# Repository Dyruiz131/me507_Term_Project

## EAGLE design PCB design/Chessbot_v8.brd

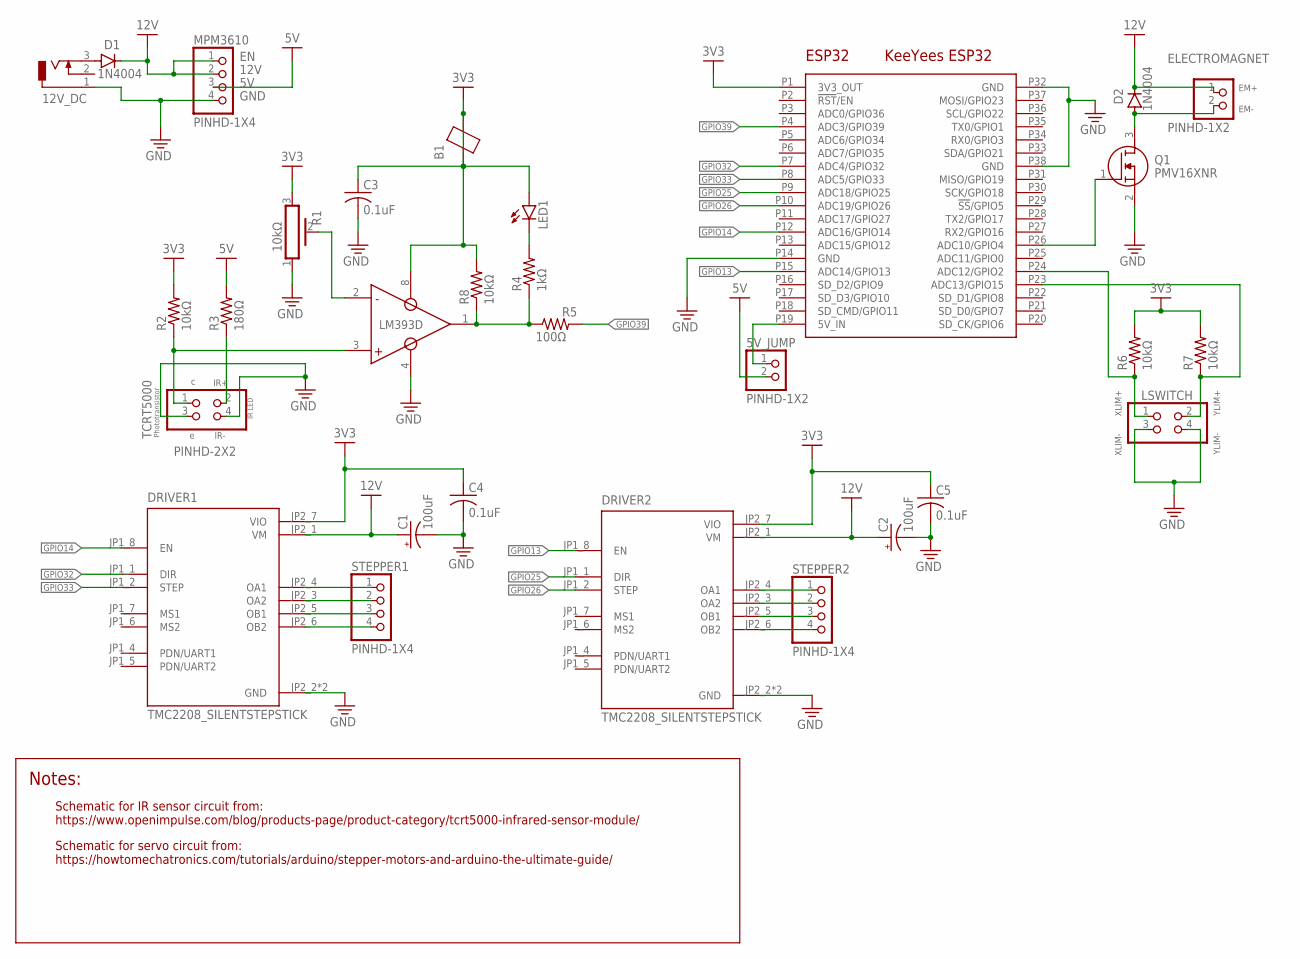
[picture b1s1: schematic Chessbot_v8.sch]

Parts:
5V_JUMP: PINHD-1X2; 1X02
12V_DC: DCJ0303
B1: BEAD0805; 0805
C1, C2: 100uF; E2,5-6
C3, C4, C5: 0.1uF; C0805
D1, D2: 1N4004; DO41-10
DRIVER1, DRIVER2: TMC2208_SILENTSTEPSTICK; MODULE_TMC2208_SILENTSTEPSTICK
ELECTROMAGNET: PINHD-1X2; 1X02
ESP32: KEEYEES_ESP32
LED1: LEDSMT1206; 1206
LSWITCH: PINHD-2X2; 2X02
MPM3610: PINHD-1X4; 1X04
Q1: PMV16XNR; SOT95P230X110-3N
R1: 10kΩ; PV36Z
R2, R6, R7, R8: 10kΩ; R0805
R3: 180Ω; R0805
R4: 1kΩ; R0805
R5: 100Ω; R0805
STEPPER1, STEPPER2: PINHD-1X4; 1X04
TCRT5000: PINHD-2X2; 2X02
U$2: LM393D

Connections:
3V3: B1.1, B1.2, C3.1, C4.1, C5.1, DRIVER1.JP2_7 (VIO), DRIVER2.JP2_7 (VIO), ESP32.P1 (3V3_OUT), LED1.A, R1.3, R2.2, R6.2, R7.2, R8.2, U$2.8 (VCC)
5V: 5V_JUMP.2, MPM3610.3, R3.2
12V: C1.+, C2.+, D1.C, D2.C, DRIVER1.JP2_1 (VM), DRIVER2.JP2_1 (VM), ELECTROMAGNET.1, MPM3610.1, MPM3610.2
GND: 12V_DC.1, C1.-, C2.-, C3.2, C4.2, C5.2, DRIVER1.JP2_2 (GND), DRIVER1.JP2_8 (GND), DRIVER2.JP2_2 (GND), DRIVER2.JP2_8 (GND), ESP32.P14 (GND), ESP32.P32 (GND), ESP32.P38 (GND), LSWITCH.3, LSWITCH.4, MPM3610.4, Q1.2 (S), R1.1, TCRT5000.3, TCRT5000.4, U$2.4 (GND)
GPIO13: DRIVER2.JP1_8 (EN), ESP32.P15 (ADC14/GPIO13)
GPIO14: DRIVER1.JP1_8 (EN), ESP32.P12 (ADC16/GPIO14)
GPIO25: DRIVER2.JP1_1 (DIR), ESP32.P9 (ADC18/GPIO25)
GPIO26: DRIVER2.JP1_2 (STEP), ESP32.P10 (ADC19/GPIO26)
GPIO32: DRIVER1.JP1_1 (DIR), ESP32.P7 (ADC4/GPIO32)
GPIO33: DRIVER1.JP1_2 (STEP), ESP32.P8 (ADC5/GPIO33)
GPIO39: ESP32.P4 (ADC3/GPIO39), R5.2
unnamed: R1.2, U$2.2 (IN-)
unnamed: DRIVER1.JP2_4 (OA1), STEPPER1.1
unnamed: DRIVER1.JP2_3 (OA2), STEPPER1.2
unnamed: R3.1, TCRT5000.2
unnamed: DRIVER1.JP2_5 (OB1), STEPPER1.3
unnamed: R2.1, TCRT5000.1, U$2.3 (IN+)
unnamed: DRIVER1.JP2_6 (OB2), STEPPER1.4
unnamed: DRIVER2.JP2_4 (OA1), STEPPER2.1
unnamed: D2.A, ELECTROMAGNET.2, Q1.3 (D)
unnamed: DRIVER2.JP2_3 (OA2), STEPPER2.2
unnamed: DRIVER2.JP2_5 (OB1), STEPPER2.3
unnamed: DRIVER2.JP2_6 (OB2), STEPPER2.4
unnamed: 5V_JUMP.1, ESP32.P19 (5V_IN)
unnamed: LED1.C, R4.2
unnamed: 12V_DC.3, D1.A
unnamed: R4.1, R5.1, R8.1, U$2.1 (OUT)
unnamed: ESP32.P26 (ADC10/GPIO4), Q1.1 (G)
unnamed: ESP32.P24 (ADC12/GPIO2), LSWITCH.1, R6.1
unnamed: ESP32.P23 (ADC13/GPIO15), LSWITCH.2, R7.1

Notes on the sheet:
12V
GND
EM+
EM-
IR+
IR-
Phototransistor
IR LED
Schematic for IR sensor circuit from: https://www.openimpulse.com/blog/products-page/product-category/tcrt5000-infrared-sensor-module/
Schematic for servo circuit from: https://howtomechatronics.com/tutorials/arduino/stepper-motors-and-arduino-the-ultimate-guide/
XLIM+
XLIM-
YLIM+
YLIM-

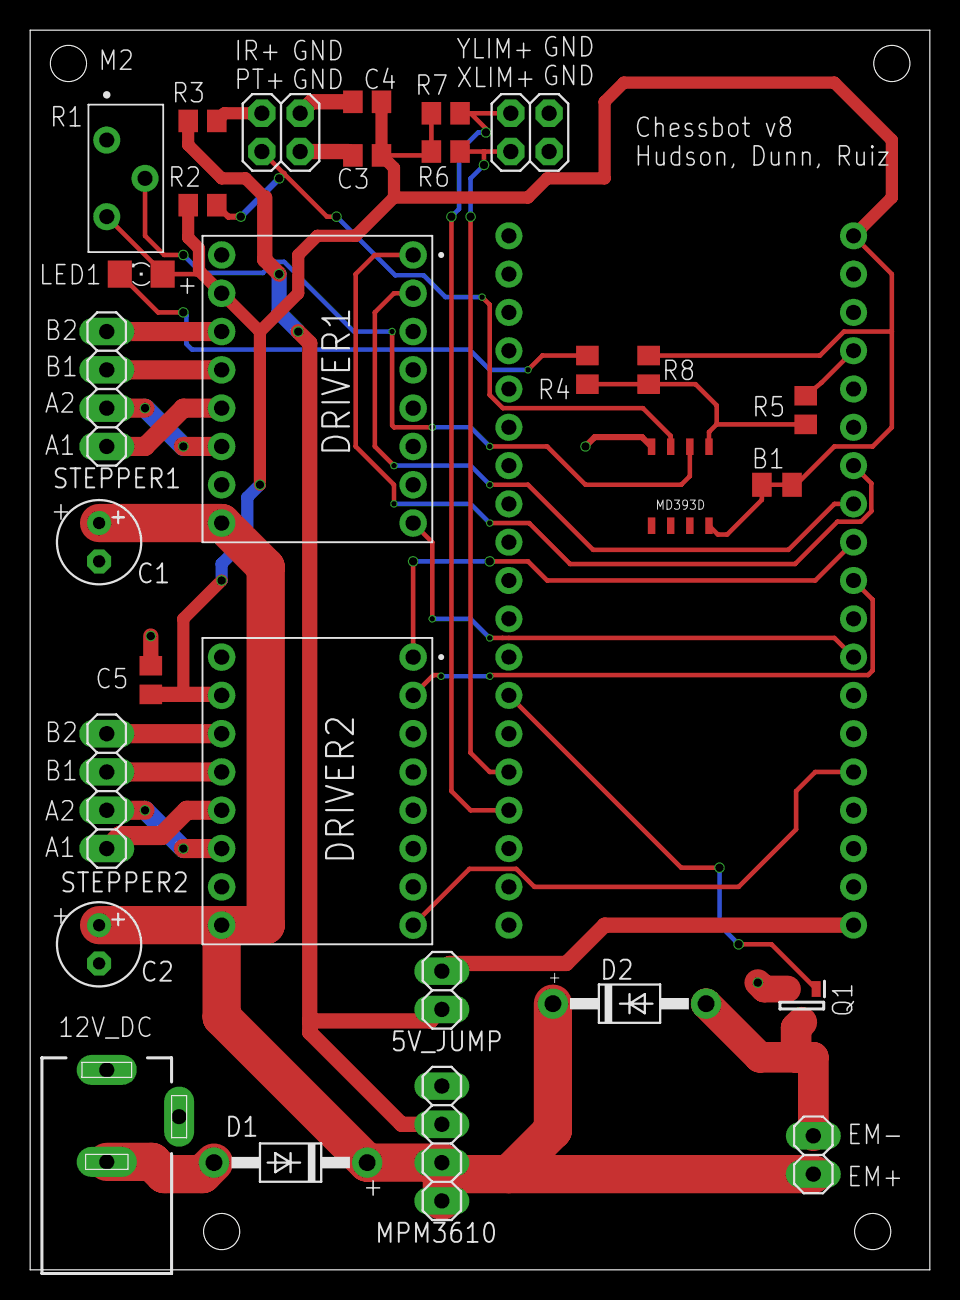
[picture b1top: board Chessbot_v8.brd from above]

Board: 2 copper layers, 59.7 x 82.2 mm, 30 parts (1 on the bottom side), 30 nets.

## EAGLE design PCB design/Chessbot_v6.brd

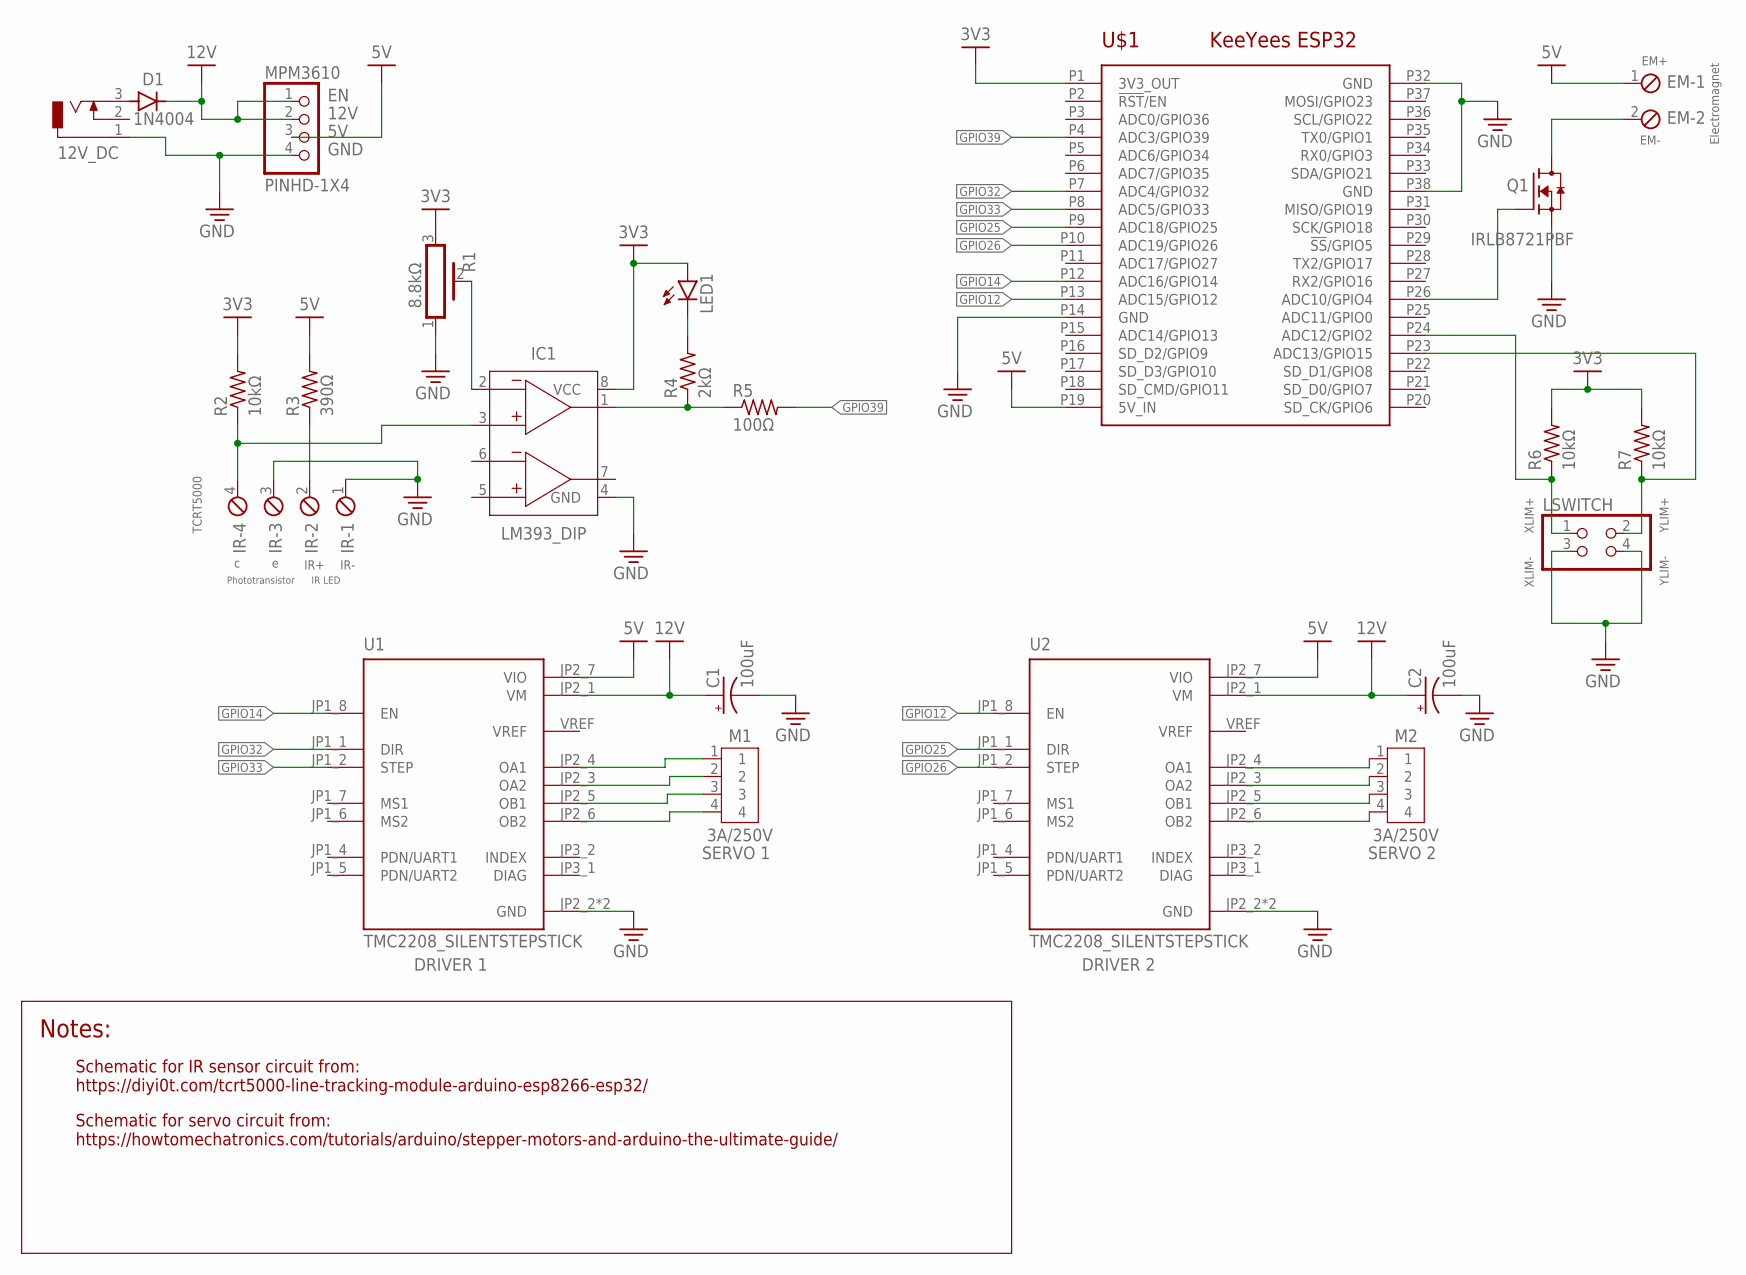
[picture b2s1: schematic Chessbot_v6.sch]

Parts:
12V_DC: DCJ0303
C1, C2: 100uF; E2,5-6
D1: 1N4004; DO41-10
EM: SCREWTERM_2P_254; 2POL254
IC1: LM393_DIP; DIP826W53P254L959H508Q8B
IR: SCREWTERM_4P_254; 4POL254
LED1: LEDSMT1206; 1206
LSWITCH: PINHD-2X2; 2X02
M1, M2: 3A/250V; B4B-XH-A
MPM3610: PINHD-1X4; 1X04
Q1: IRLB8721PBF; TO254P1067X483X2057-3
R1: 8.8kΩ; PV36Z
R2, R6, R7: 10kΩ; R0805
R3: 390Ω; R0805
R4: 2kΩ; R0805
R5: 100Ω; R0805
U1, U2: TMC2208_SILENTSTEPSTICK; MODULE_TMC2208_SILENTSTEPSTICK
U$1: KEEYEES_ESP32EXT; KEEYEES_ESP32_EXTENDED

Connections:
3V3: IC1.8 (VCC), LED1.A, R1.3, R2.2, R6.2, R7.2, U$1.P1 (3V3_OUT)
5V: EM.1, MPM3610.3, R3.2, U1.JP2_7 (VIO), U2.JP2_7 (VIO), U$1.P19 (5V_IN)
12V: C1.+, C2.+, D1.C, MPM3610.1, MPM3610.2, U1.JP2_1 (VM), U2.JP2_1 (VM)
GND: 12V_DC.1, C1.-, C2.-, IC1.4 (GND), IR.1, IR.3, LSWITCH.3, LSWITCH.4, MPM3610.4, Q1.3 (S), R1.1, U1.JP2_2 (GND), U1.JP2_8 (GND), U2.JP2_2 (GND), U2.JP2_8 (GND), U$1.P14 (GND), U$1.P32 (GND), U$1.P38 (GND)
GPIO12: U2.JP1_8 (EN), U$1.P13 (ADC15/GPIO12)
GPIO14: U1.JP1_8 (EN), U$1.P12 (ADC16/GPIO14)
GPIO25: U2.JP1_1 (DIR), U$1.P9 (ADC18/GPIO25)
GPIO26: U2.JP1_2 (STEP), U$1.P10 (ADC19/GPIO26)
GPIO32: U1.JP1_1 (DIR), U$1.P7 (ADC4/GPIO32)
GPIO33: U1.JP1_2 (STEP), U$1.P8 (ADC5/GPIO33)
GPIO39: R5.2, U$1.P4 (ADC3/GPIO39)
unnamed: M2.1, U2.JP2_4 (OA1)
unnamed: IC1.2 (-IN1), R1.2
unnamed: M2.2, U2.JP2_3 (OA2)
unnamed: IR.2, R3.1
unnamed: M2.3, U2.JP2_5 (OB1)
unnamed: IC1.3 (+IN1), IR.4, R2.1
unnamed: M2.4, U2.JP2_6 (OB2)
unnamed: M1.1, U1.JP2_4 (OA1)
unnamed: EM.2, Q1.2 (D)
unnamed: M1.2, U1.JP2_3 (OA2)
unnamed: M1.3, U1.JP2_5 (OB1)
unnamed: M1.4, U1.JP2_6 (OB2)
unnamed: IC1.1 (OUT1), R4.1, R5.1
unnamed: LED1.C, R4.2
unnamed: 12V_DC.3, D1.A
unnamed: Q1.1 (G), U$1.P26 (ADC10/GPIO4)
unnamed: LSWITCH.1, R6.1, U$1.P24 (ADC12/GPIO2)
unnamed: LSWITCH.2, R7.1, U$1.P23 (ADC13/GPIO15)

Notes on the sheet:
12V
GND
EM+
EM-
TCRT5000
IR+
IR-
Electromagnet
SERVO 1
SERVO 2
DRIVER 1
DRIVER 2
Phototransistor
IR LED
Schematic for IR sensor circuit from: https://diyi0t.com/tcrt5000-line-tracking-module-arduino-esp8266-esp32/
Schematic for servo circuit from: https://howtomechatronics.com/tutorials/arduino/stepper-motors-and-arduino-the-ultimate-guide/
XLIM+
XLIM-
YLIM+
YLIM-

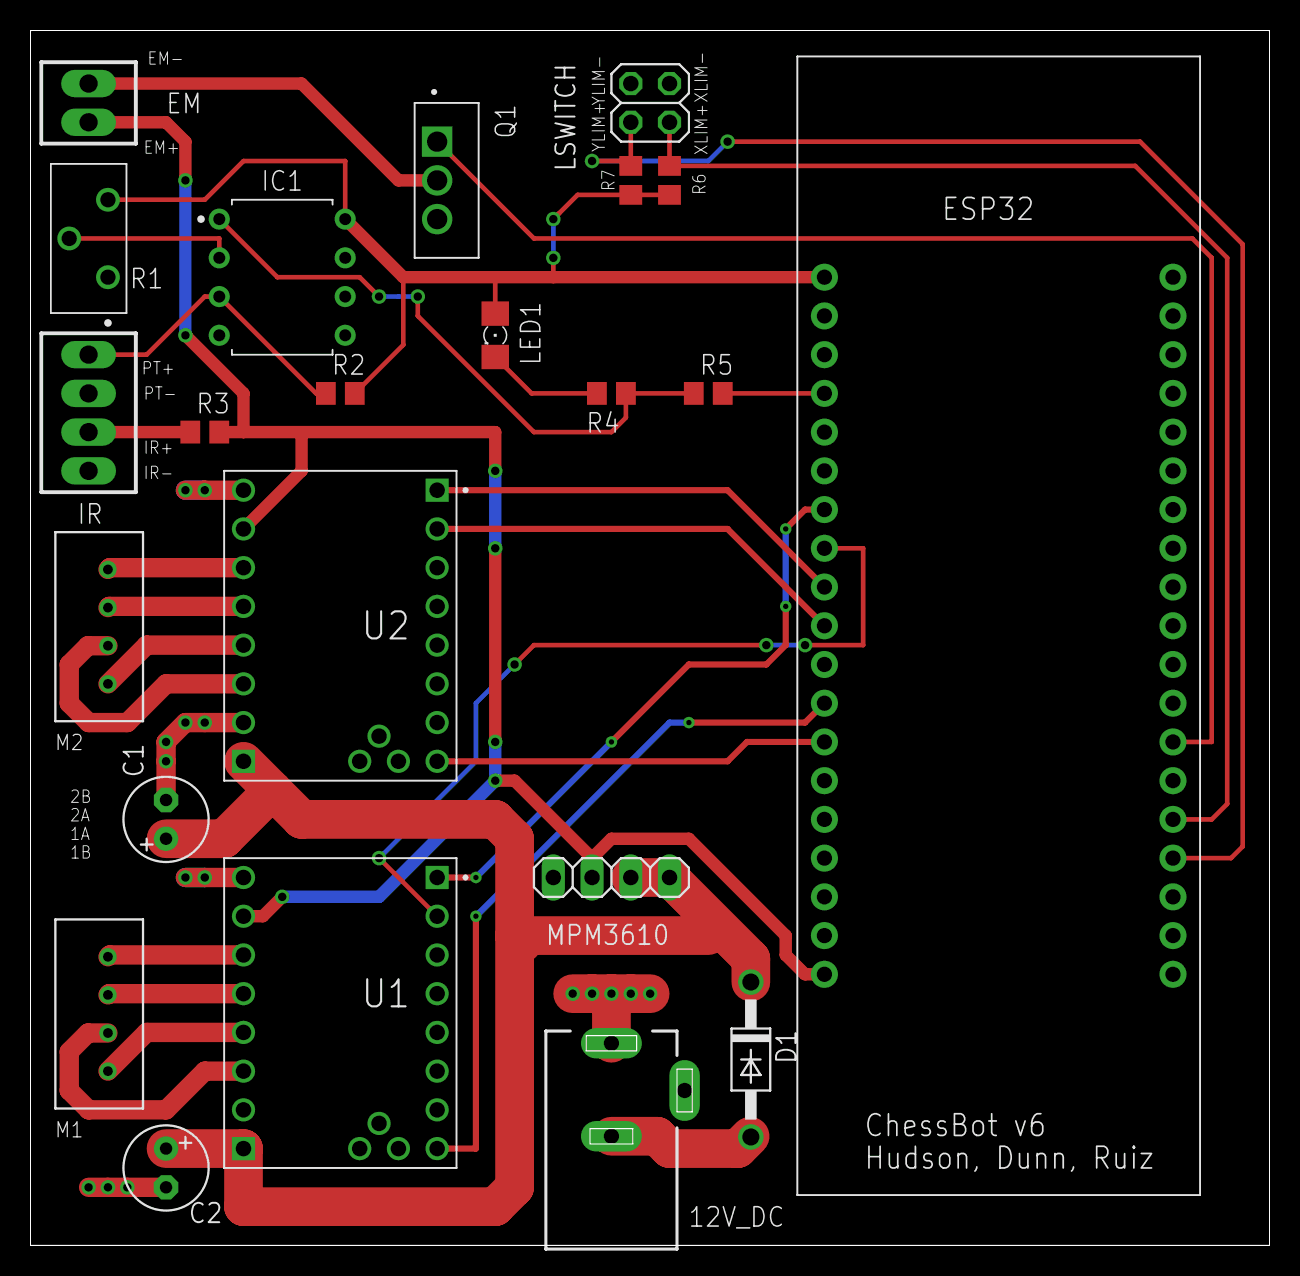
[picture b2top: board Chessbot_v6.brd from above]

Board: 2 copper layers, 81.3 x 79.7 mm, 23 parts (0 on the bottom side), 29 nets.

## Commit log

2022-10-12 Added eagle project
2022-10-12 first pack&go
    contains platform, linear rail and carriage
2022-10-12 update
    added the rail supports
2022-10-13 Added Gantry Kinematics
2022-10-14 Chessbot board design v5
    New design with schematic and board.
2022-10-15 v6 board - added limit switches
2022-10-21 Board v7 design
2022-10-23 Minor design alterations
2022-10-23 DRC passed, CAM files
2022-10-24 added the game board
2022-10-25 V8 design
2022-10-27 Chessbot v8 gerber
2022-11-01 Motor_Driver
2022-11-02 Workspace Push
2022-11-02 Added gitignore
2022-11-02 Parts lists
2022-11-02 Test_file
2022-11-09 Stepper mount design with updated system assembly
2022-11-10 Shares demo
2022-11-10 Started mover task implemetation
2022-11-10 Origin move sequence method
2022-11-10 update
    added the MS1 and MS2 output definitions
    changed task kill to depend on limit switch state
    changed limit switch configurations in SW
2022-11-11 Linear actuator Mount
2022-11-14 fix: Bugs after merging mover branch
2022-11-17 updated the stepper mounts
2022-11-17 latest assembly
2022-11-18 updated assembly and stepper mount
2022-11-19 stepper support update
2022-11-19 updated the idler pulley support
2022-11-22 Mover Task Complete
2022-11-22 feat: create api branch
2022-11-24 Created Motor Task and updated Mover Task
2022-11-26 feat: Controller website complete
2022-11-26 Moved Chessbot server to own repo for deployment
2022-11-27 ScanBoard Task
    Finished Scan Board Task
2022-11-27 APIHandler complete
2022-11-27 Started integrating API
2022-11-27 Rename README to README.md
2022-11-27 Added TCRT5000L model
2022-11-27 updated full assembly and the rail to rail idler mounts
2022-11-28 Solenoid mount update
2022-11-28 Belt clamp axis alignment
2022-11-28 added a limit switch to a rail-rail idler mount and modified the actuator mount
2022-11-28 updated the assembly for the solenoid mounts
2022-11-29 Refactoring of original code
2022-11-30 Updated naming
2022-11-30 Renaming
2022-11-30 Changed folder names
2022-11-30 Code progression
2022-12-01 11/30 push
2022-12-01 fix wifi bugs
2022-12-01 Init
2022-12-01 fix: class constructors
2022-12-01 FetchMoveTask implemented
2022-12-01 Kinematics update
2022-12-01 FetchMoveTask
2022-12-01 v1.0 release
2022-12-01 Bug fixing on hardware
2022-12-01 while loops out
2022-12-01 APIHandlerFix
2022-12-01 v1.1
2022-12-01 v1.2
2022-12-01 v1.2.1
2022-12-01 fix: issue when starting with ongoing game
2022-12-01 Bug fixes
2022-12-01 Print statement changes
2022-12-01 New branch
2022-12-01 Added wifi pass
2022-12-01 Wifi pass
2022-12-02 tuned and working!!!
2022-12-02 fix api move complete issue
2022-12-02 Added more comments
2022-12-02 solenoid fix
2022-12-06 Trimmed controller task
2022-12-06 docs: doxygen comments complete
2022-12-07 docs: more comments
2022-12-07 docs: comments finalised
2022-12-07 concise
2022-12-07 Changed some variable names
2022-12-07 Doxygen documentation
2022-12-07 Docs at root
2022-12-07 Updated Task Diagram and Kinematics
2022-12-07 Added private variables to docs
2022-12-07 Fixed docs error
2022-12-07 Moved docs to root
2022-12-07 Docs upload
2022-12-07 Upload docs again
2022-12-07 doxygen config update
